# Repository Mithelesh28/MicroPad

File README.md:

# Macropad

A custom 6-key macropad built around the Seeed Studio XIAO RP2040, featuring two rotary encoders, RGB lighting, and Cherry MX mechanical switches.

## Features

* 6 programmable mechanical keys
* 2 rotary encoders with push-switch support
* 2 SK6812 MINI-E RGB LEDs
* USB-C connectivity via Seeed Studio XIAO RP2040
* Custom PCB designed in KiCad 9
* Custom enclosure designed in Fusion 360
* KMK firmware support

## Hardware

### Microcontroller

* Seeed Studio XIAO RP2040

### Switches

* 6 × Cherry MX compatible switches

### Rotary Encoders

* 2 × EC11 rotary encoders

### RGB Lighting

* 2 × SK6812 MINI-E addressable RGB LEDs

## Key Layout

| Key | Function         |
| --- | ---------------- |
| SW3 | D                |
| SW4 | Copy (Ctrl + C)  |
| SW5 | S                |
| SW6 | W                |
| SW7 | A                |
| SW8 | Paste (Ctrl + V) |

## Encoder Functions

### Encoder 1

* Clockwise → Volume Up
* Counter-clockwise → Volume Down

### Encoder 2

* Clockwise → Brightness Up
* Counter-clockwise → Brightness Down

## PCB Design

Designed using KiCad 9.

### Main Components

* Seeed Studio XIAO RP2040
* Cherry MX footprints
* EC11 rotary encoders
* SK6812 MINI-E RGB LEDs

## Firmware

Planned firmware stack:

* CircuitPython
* KMK Firmware

The firmware will support:

* Custom key mappings
* Rotary encoder controls
* RGB effects
* Media controls

## CAD

The enclosure and assembly are designed in Fusion 360.

## Manufacturing Files

This repository contains:

* KiCad project files
* PCB manufacturing files (Gerbers)
* STEP assembly model
* Fusion 360 enclosure files
* Firmware source code

## Future Improvements

* Additional RGB effects
* Multiple layers and macros
* OLED display support
* Custom encoder functions
* VIA/Vial compatibility

## License

MIT License

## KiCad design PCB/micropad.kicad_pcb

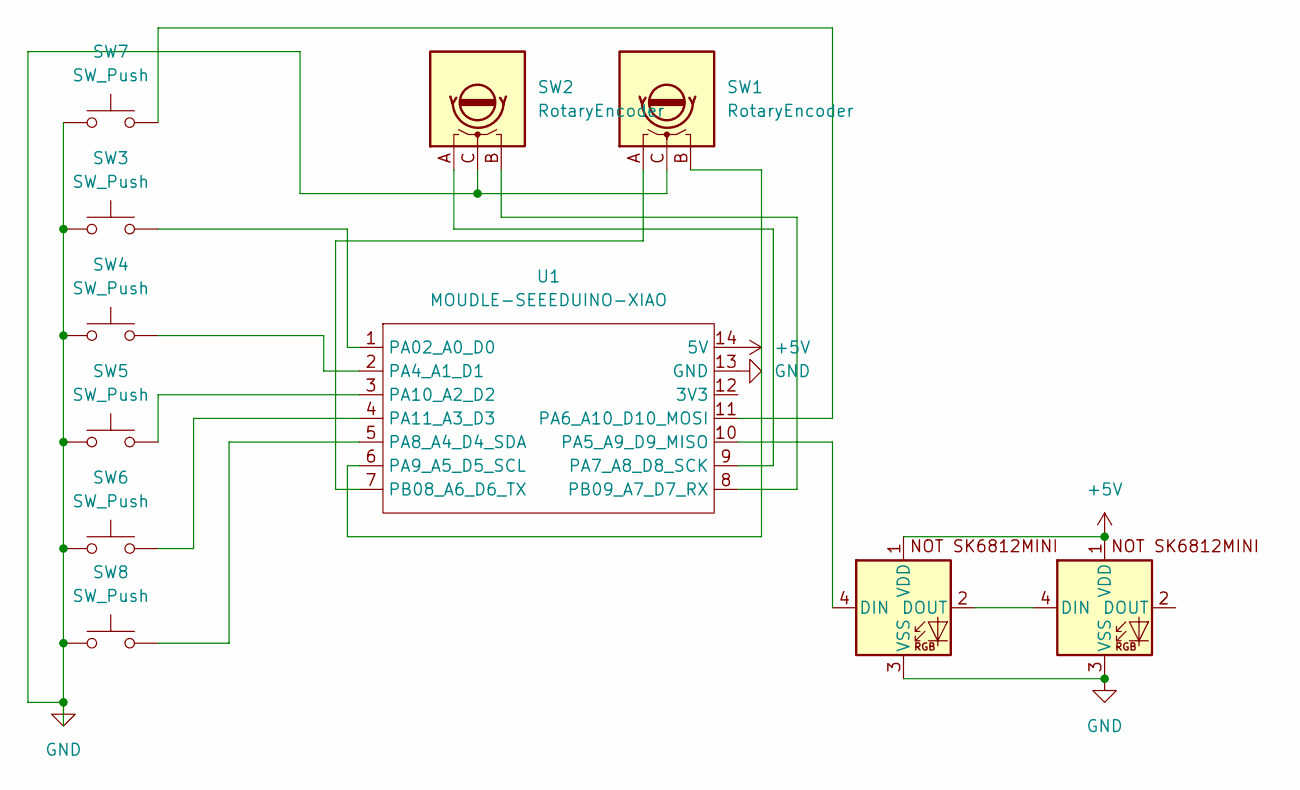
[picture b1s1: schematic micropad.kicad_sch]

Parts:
D1, D2: SK6812MINI-E; LED_SK6812MINI_PLCC4_3.5x3.5mm_P1.75mm
SW1: RotaryEncoder; RotaryEncoder_Alps_EC11E-Switch_Vertical_H20mm
SW2: RotaryEncoder; RotaryEncoder_Alps_EC11E-Switch_Vertical_H20mm_CircularMoun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
SW3, SW4, SW5, SW6, SW7, SW8: SW_Push; SW_Cherry_MX_1.00u_PCB
U1: MOUDLE-SEEEDUINO-XIAO; XIAO-Generic-Hybrid-14P-2.54-21X17.8MM

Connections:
+5V: D1.1 (VDD), D2.1 (VDD), U1.14 (5V)
GND: D1.3 (VSS), D2.3 (VSS), SW1.C, SW2.C, SW3.1, SW4.1, SW5.1, SW6.1, SW7.1, SW8.1, U1.13 (GND)
unnamed: D1.4 (DIN), D2.2 (DOUT)
unnamed: D2.4 (DIN), U1.10 (PA5_A9_D9_MISO)
unnamed: SW3.2, U1.1 (PA02_A0_D0)
unnamed: SW4.2, U1.2 (PA4_A1_D1)
unnamed: SW7.2, U1.11 (PA6_A10_D10_MOSI)
unnamed: SW2.A, U1.9 (PA7_A8_D8_SCK)
unnamed: SW8.2, U1.5 (PA8_A4_D4_SDA)
unnamed: SW1.B, U1.6 (PA9_A5_D5_SCL)
unnamed: SW5.2, U1.3 (PA10_A2_D2)
unnamed: SW6.2, U1.4 (PA11_A3_D3)
unnamed: SW1.A, U1.7 (PB08_A6_D6_TX)
unnamed: SW2.B, U1.8 (PB09_A7_D7_RX)

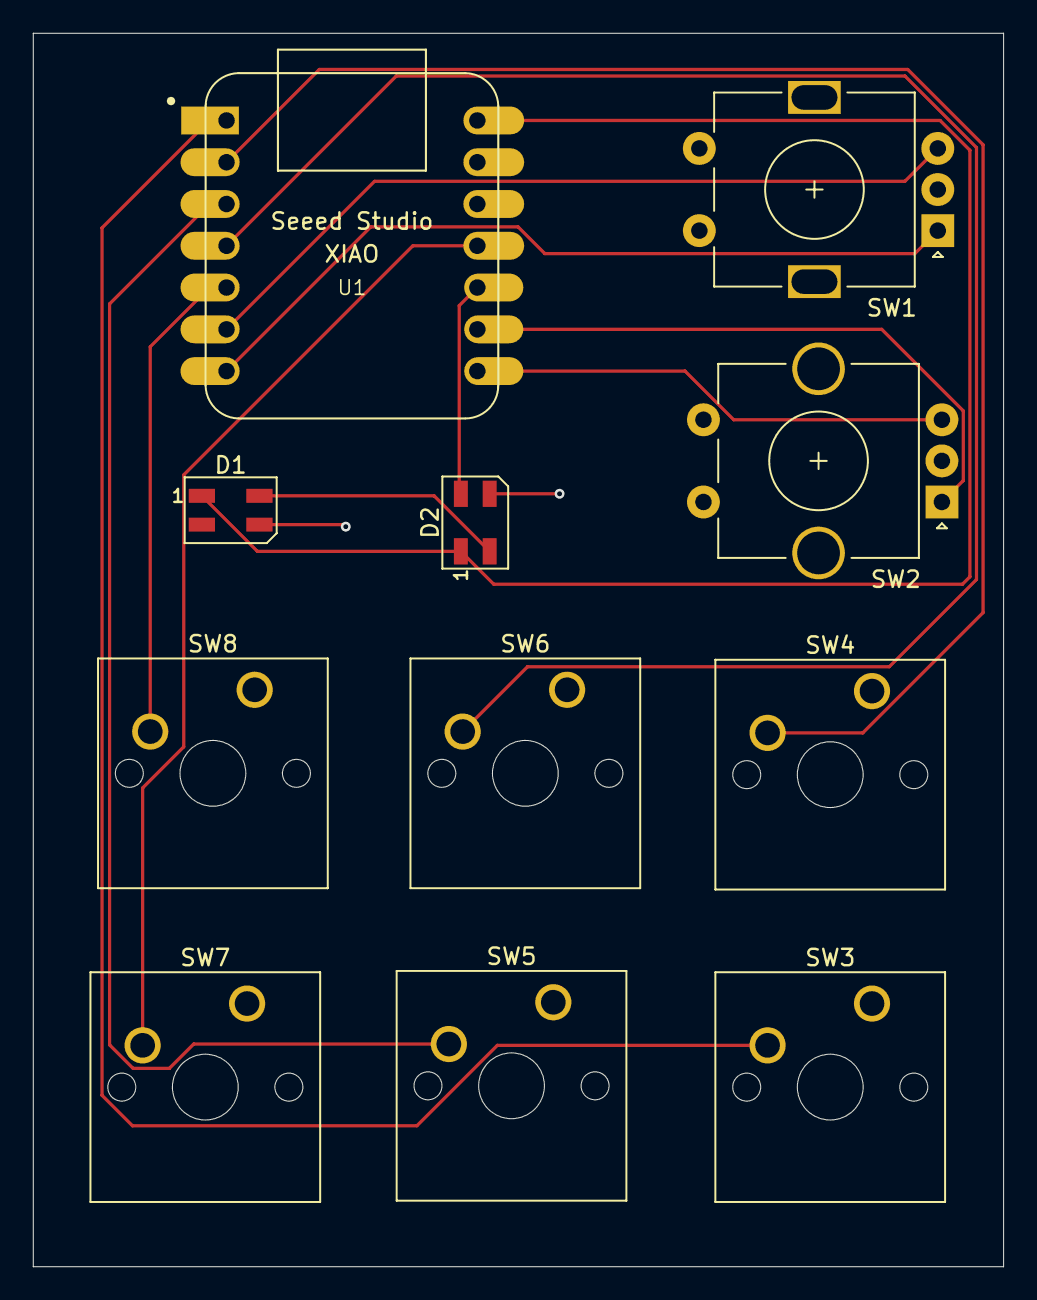
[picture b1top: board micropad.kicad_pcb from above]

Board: 2 copper layers, 59.0 x 75.0 mm, 11 parts (0 on the bottom side), 14 nets.

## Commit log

2026-06-03 micropad PCB is done
2026-06-03 Revise README for Micropad project details
    Updated project name and added detailed features, hardware specifications, key layout, encoder functions, PCB design, firmware stack, CAD design, manufacturing files, and future improvements.
2026-06-03 editing a readme
2026-06-03 adding the CAD file
